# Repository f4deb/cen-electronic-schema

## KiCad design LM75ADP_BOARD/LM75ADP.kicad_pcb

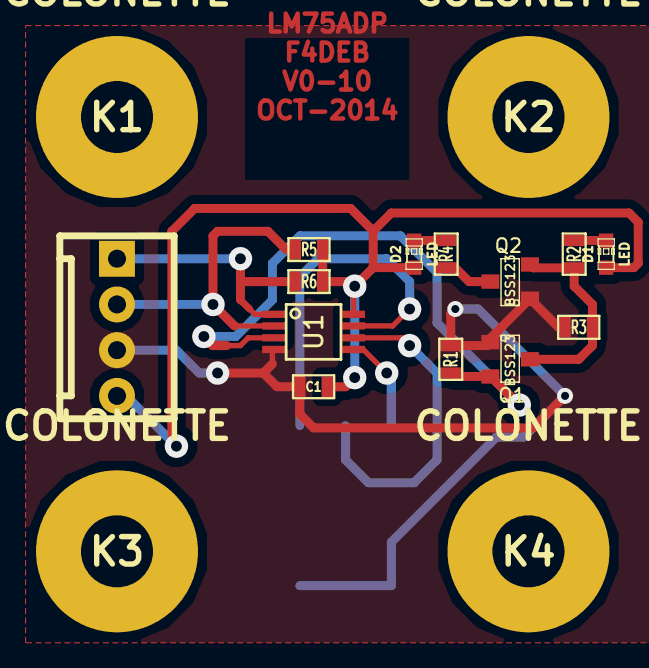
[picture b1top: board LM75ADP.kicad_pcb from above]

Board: 2 copper layers, 18 parts (1 on the bottom side), 12 nets.

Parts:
C1: 100n; SM0603_Capa
D1, D2: LED; LED-0603
K1, K2, K3, K4: COLONETTE
P1: CONN_4; KK-4
Q1, Q2: BSS123; SOT23
R1, R3: 470k; SM0603_Resistor
R2, R4: 3k3; SM0603_Resistor
R5, R6: 10k; SM0603_Resistor
SW1: SWITCH_X_4; SWCMS4
U1: LM75A; SSOP8

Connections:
/SCL: P1.2, R5.2, U1.2
/SDA: P1.1, R6.2, U1.1
GND: C1.2, P1.3, Q1.1, Q2.1, R1.2, R3.2, SW1.1, SW1.2, SW1.3, U1.4
unnamed: Q1.2, R1.1, U1.3
unnamed: Q1.3, Q2.2, R2.2, R3.1
unnamed: SW1.8, U1.5
unnamed: SW1.7, U1.6
unnamed: SW1.6, U1.7
unnamed: D2.2, R4.1
unnamed: Q2.3, R4.2
unnamed: D1.2, R2.1
VCC: C1.1, D1.1, D2.1, P1.4, R5.1, R6.1, U1.8

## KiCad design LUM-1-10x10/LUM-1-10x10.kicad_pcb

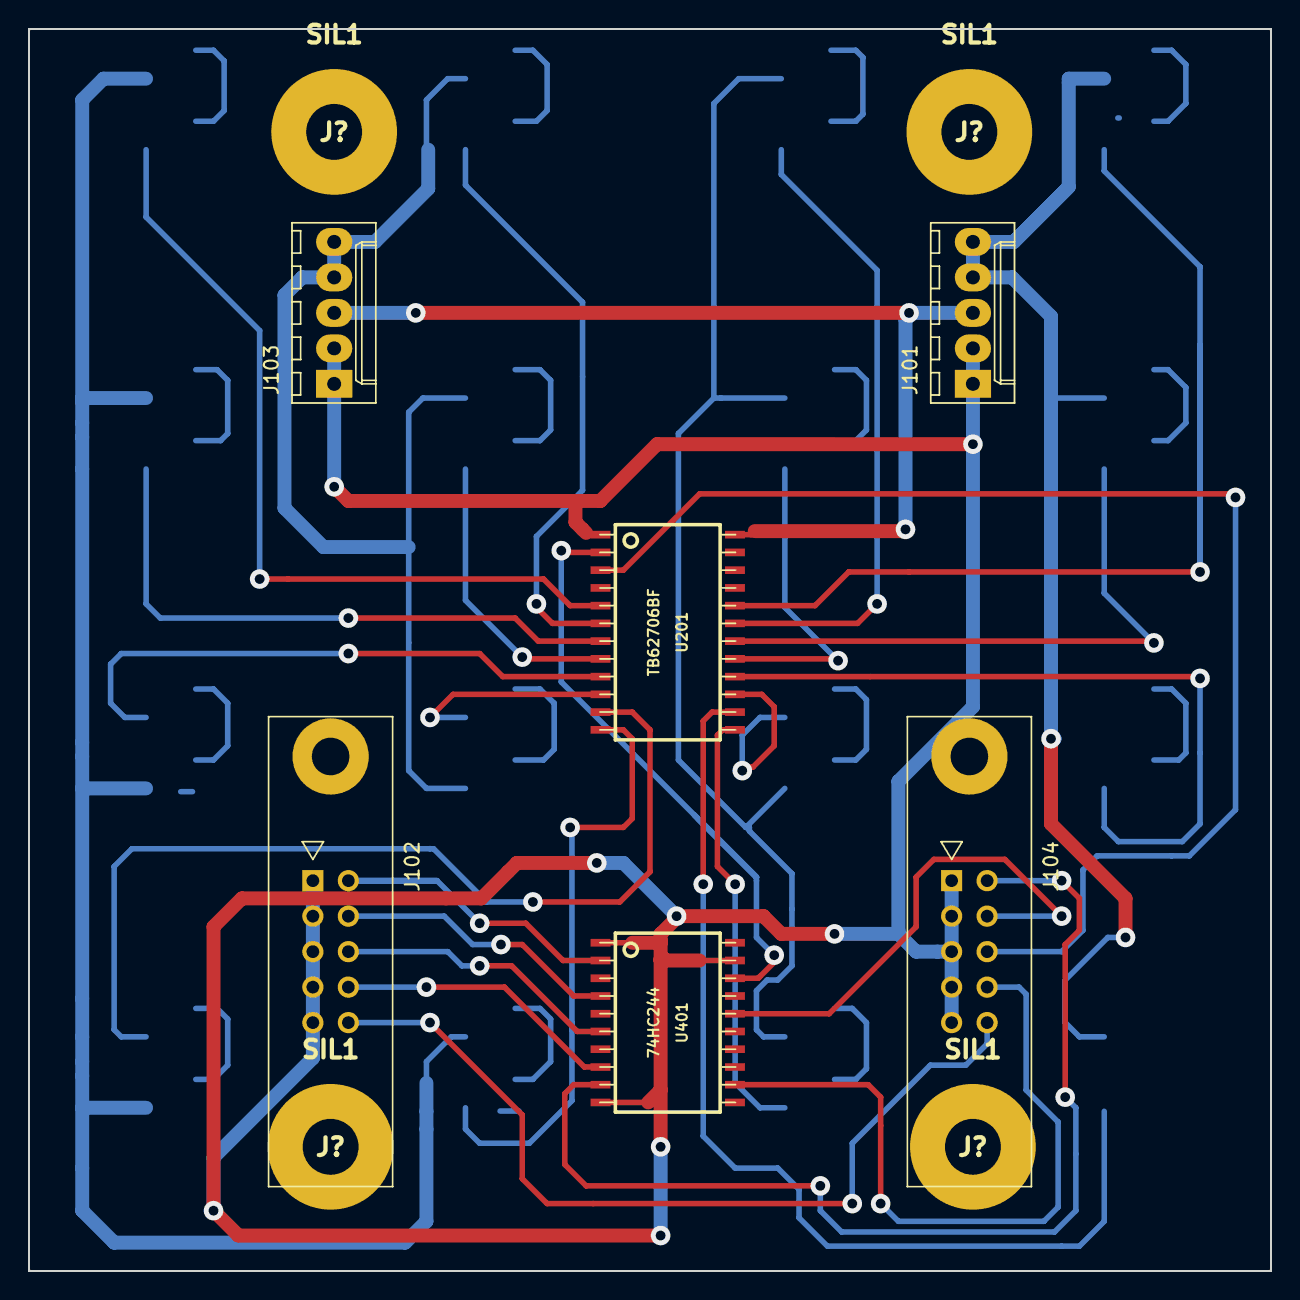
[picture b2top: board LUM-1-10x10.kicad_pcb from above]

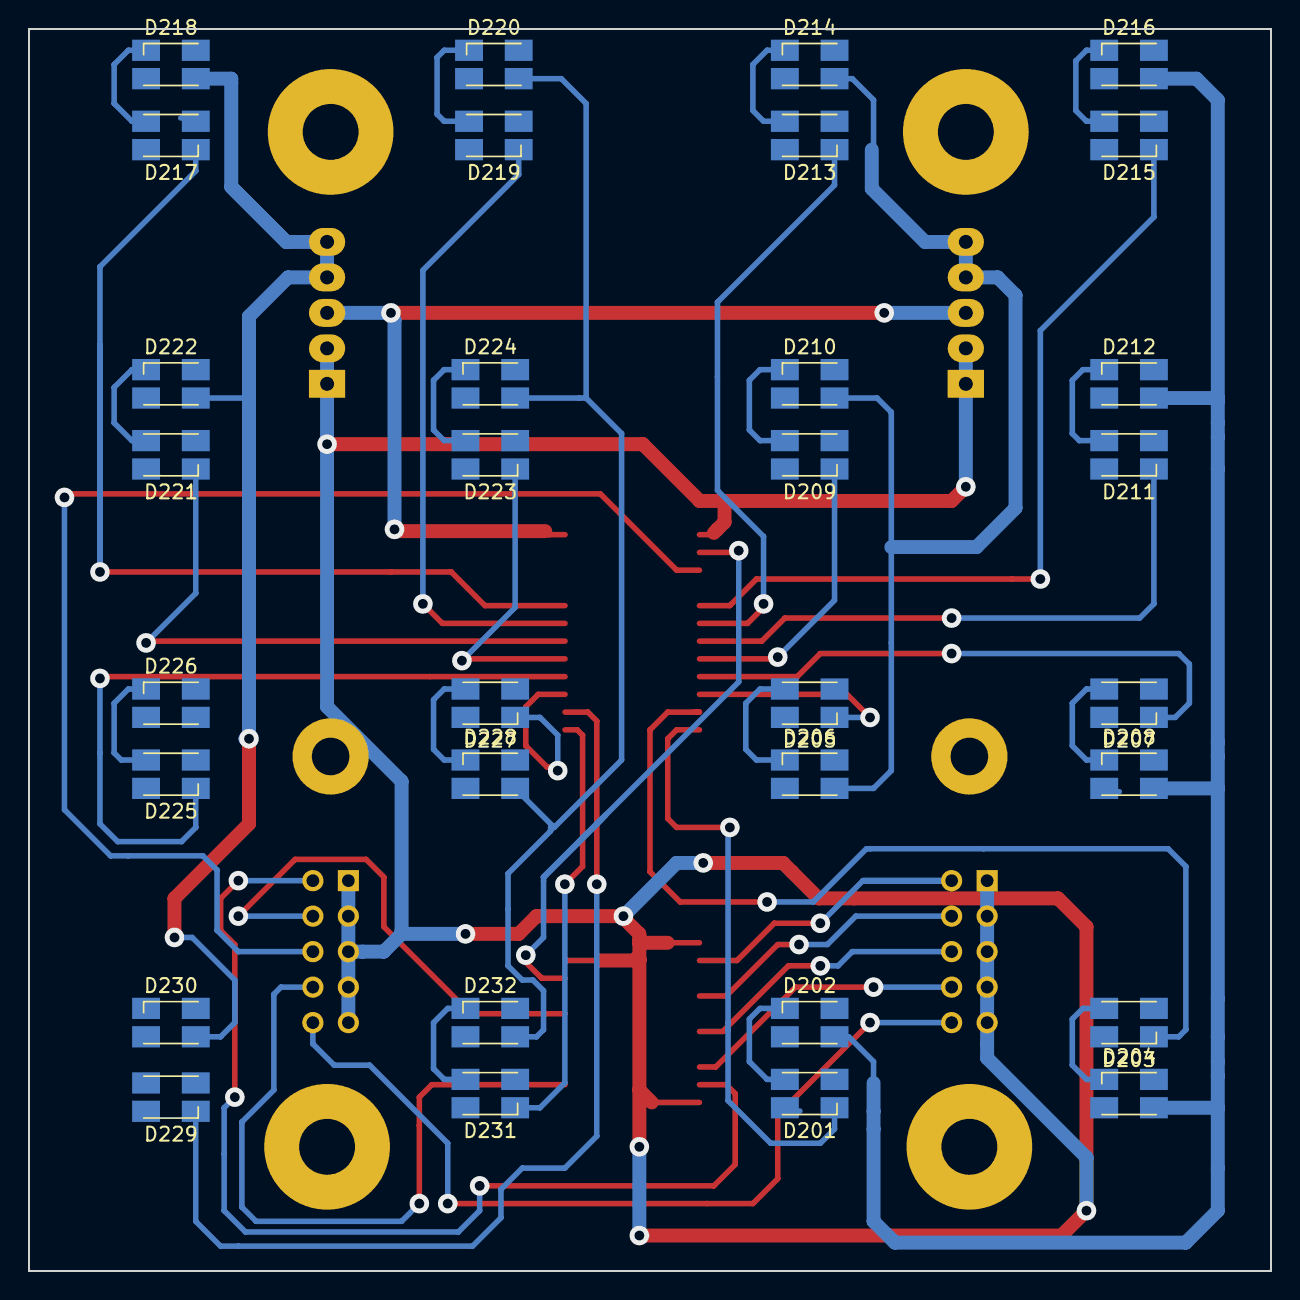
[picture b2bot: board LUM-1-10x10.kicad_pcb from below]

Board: 2 copper layers, 88.9 x 88.9 mm, 42 parts (32 on the bottom side), 45 nets.

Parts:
D201, D203, D205, D207, D209, D211, D213, D215, D217, D219, D221, D223, D225, D227, D229, D231: LED; LED_Cree-PLCC4_3.2x2.8mm_CCW
D202, D204, D206, D208, D210, D212, D214, D216, D218, D220, D222, D224, D226, D228, D230, D232: LED_PLCC_4; LED_Cree-PLCC4_3.2x2.8mm_CCW
J101, J103: CONN_01X05; Molex_KK-6410-05_05x2.54mm_Straight
J102, J104: CONN_02X05; he10-10d
J?: SIL1; COLONETTE
J?#2, J?#3, J?#4: SIL1; COLONETTE
U201: TB62706BF; soic-24
U401: 74HC244; soic-20

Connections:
+5V: D202.3, D204.3, D206.3, D208.3, D210.3, D212.3, D214.3, D216.3, D218.3, D220.3, D222.3, D224.3, D226.3, D228.3, D230.3, D232.3, J101.4, J101.5, J103.4, J103.5
+5VD: J101.3, J103.3, U201.24
/CLK: J104.6, U201.3, U401.14
/CLKA: J102.6, U401.6
/EN: J104.4, U401.16
/ENA: J102.4, U401.4
/LAT: J104.8, U401.12
/LATA: J102.8, U401.8
/RET: J102.10, J104.10
/S1: U201.2, U401.18
/S1A: J102.2, U401.2
/S5B: J104.2, U401.9
GND: J101.1, J101.2, J102.1, J102.3, J102.5, J102.7, J102.9, J103.1, J103.2, J104.1, J104.3, J104.5, J104.7, J104.9, U201.1, U401.1, U401.10, U401.19
unnamed: D201.1, U201.12
unnamed: D201.3, D202.1
unnamed: D203.1, U201.11
unnamed: D203.3, D204.1
unnamed: D205.1, U201.10
unnamed: D205.3, D206.1
unnamed: D207.1, U201.9
unnamed: D207.3, D208.1
unnamed: D209.1, U201.8
unnamed: D209.3, D210.1
unnamed: D211.1, U201.7
unnamed: D211.3, D212.1
unnamed: D213.1, U201.6
unnamed: D213.3, D214.1
unnamed: D215.1, U201.5
unnamed: D215.3, D216.1
unnamed: D217.1, U201.20
unnamed: D217.3, D218.1
unnamed: D219.1, U201.19
unnamed: D219.3, D220.1
unnamed: D221.1, U201.18
unnamed: D221.3, D222.1
unnamed: D223.1, U201.17
unnamed: D223.3, D224.1
unnamed: D225.1, U201.16
unnamed: D225.3, D226.1
unnamed: D227.1, U201.15
unnamed: D227.3, D228.1
unnamed: D229.1, U201.14
unnamed: D229.3, D230.1
unnamed: D231.1, U201.13
unnamed: D231.3, D232.1

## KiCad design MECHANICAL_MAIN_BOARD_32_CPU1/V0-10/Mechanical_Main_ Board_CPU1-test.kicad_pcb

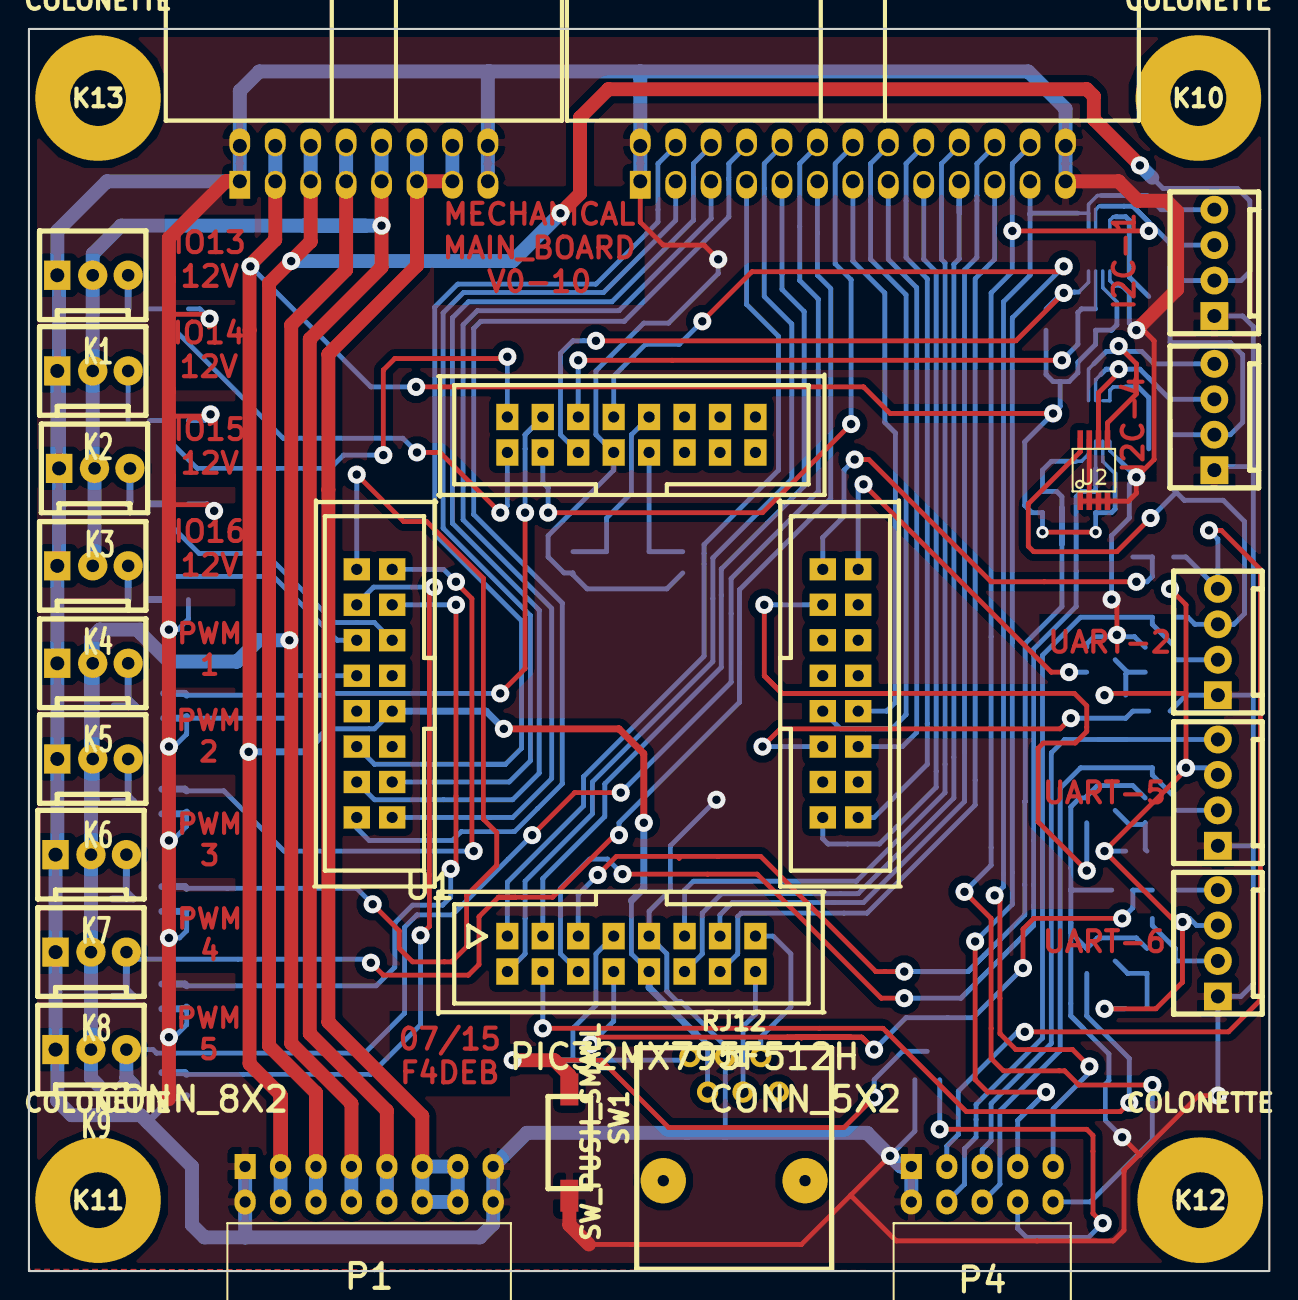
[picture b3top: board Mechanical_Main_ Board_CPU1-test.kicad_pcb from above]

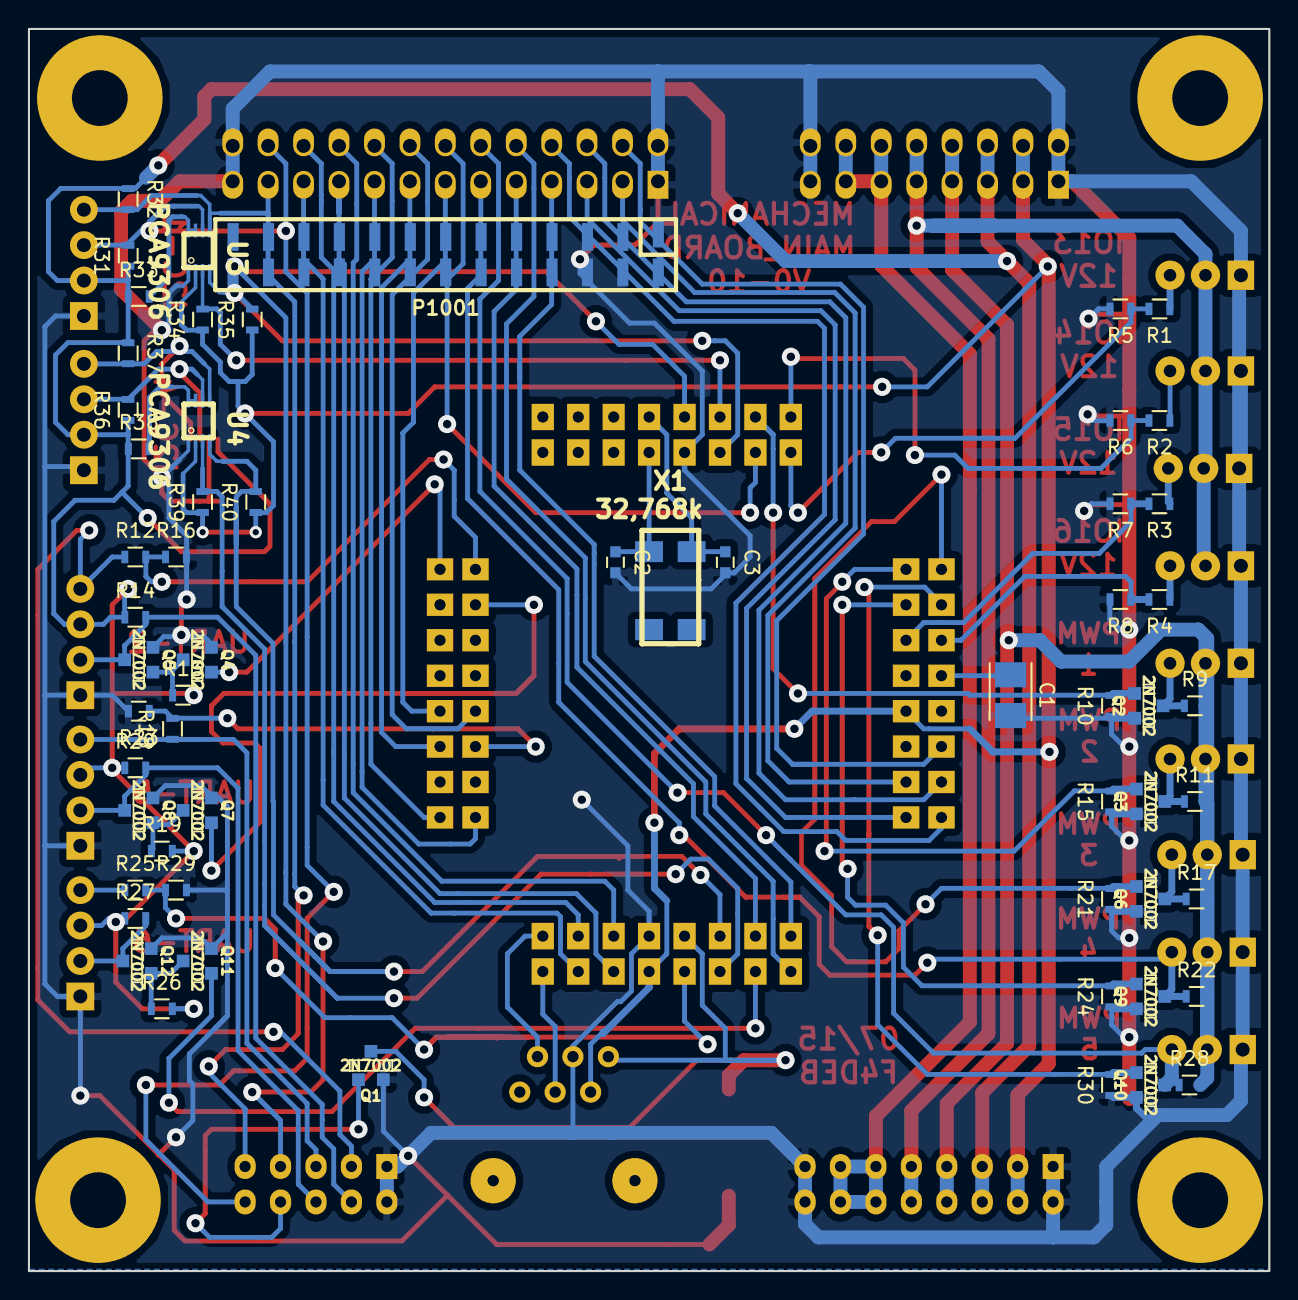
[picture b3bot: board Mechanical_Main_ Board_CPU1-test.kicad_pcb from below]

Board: 2 copper layers, 88.9 x 89.0 mm, 85 parts (59 on the bottom side), 68 nets.

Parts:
C1: 10u; TantalC_SizeB_EIA-3528_Reflow
C2, C3: 10p; C_0603
J1: RJ12
K1, K2, K3, K4, K5, K6, K7, K8, K9: CONN_3; KK-3
K10, K11, K12, K13: COLONETTE
P1: CONN_8X2; HE10-16-F-C
P2: CONN_8X2; vasch_strip_8x2_90
P3: CONN_13X2; vasch_strip_13x2_90
P4: CONN_5X2; HE10-10-F-C
P5, P6, P7, P8, P9: CONN_4; KK-4
P1001: CONN_13X2; pin_strip_13x2
Q1, Q2, Q3, Q4, Q5, Q6, Q7, Q8, Q9, Q10, Q11, Q12: 2N7002; SOT23GDS
R1, R3, R4: 47k; R_0603
R2: R47k; R_0603
R5, R6, R7, R8: 18k; R_0603
R9, R11, R13, R14, R17, R19, R20, R22, R26, R27, R28: 10k; R_0603
R10, R15, R21, R24, R30: 470k; R_0603
R12, R18, R25: 12k; R_0603
R16, R23, R29: 22k; R_0603
R31, R32, R34, R35, R36, R37, R39, R40: 2.1k; R_0603
R33, R38: 200k; R_0603
SW1: SW_PUSH_SMALL; SW2
U1: PIC32MX795F512H; PIC32_64
U2: 24C512; SSOP8
U3, U4: PCA9306; VSSOP-8
X1: 32,768k; LFXTAL003000

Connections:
+3V3: J1.2, P1.3, P1.4, P2.3, P2.4, R34.1, R35.1, R39.1, R40.1, U1.10, U1.57, U3.2, U4.2
+5V: K5.2, K6.2, K7.2, K8.2, K9.2, P1.7, P1.8, P2.7, P2.8, R9.2, R11.2, R17.2, R22.2, R28.2
+5VD: P1.5, P1.6, P2.5, P2.6, P5.3, P6.3, P7.3, P8.2, P9.2, R13.2, R14.1, R19.2, R20.1, R26.2, R27.1, R31.1, R32.1, R33.1, R36.1, R37.1, R38.1, U2.8
+12V: K1.2, K2.2, K3.2, K4.2, P1.9, P1.10, P2.9, P2.10
+15V: P1.11, P1.12, P1.13, P1.14, P2.11, P2.12, P2.13, P2.14
/INT1: P4.7, U1.42
/INT4: P3.14, P1001.14, U1.45
/IO1: P3.21, P1001.21, U1.14
/IO2: P3.22, P1001.22, U1.13
/IO3: P3.19, P1001.19, U1.12
/IO4: P3.20, P1001.20, U1.11
/IO5: P3.17, P1001.17, U1.17
/IO6: P3.18, P1001.18, U1.18
/IO7: P3.15, P1001.15, U1.22
/IO8: P3.16, P1001.16, U1.23
/IO9: P3.13, P1001.13, U1.24
/IO13: R1.2, R5.1, U1.47
/IO14: R2.2, R6.1, U1.48
/IO15: R3.2, R7.1, U1.53
/IO16: R4.2, R8.1, U1.54
/IO18: P3.4, P1001.4, U1.60
/IO19: P3.3, P1001.3, U1.61
/IO20: P3.6, P1001.6, U1.62
/IO21: P3.5, P1001.5, U1.63
/IO22: P3.8, P1001.8, U1.64
/IO23: P3.7, P1001.7, U1.1
/IO24: P3.10, P1001.10, U1.2
/IO25: P3.9, P1001.9, U1.3
/OC1: R10.2, U1.46
/OC1-5V: K5.3, R9.1
/OC2: R15.2, U1.49
/OC2-5V: K6.3, R11.1
/OC3: R21.2, U1.50
/OC4: R24.2, U1.51
/OC4-5V: K8.3, P3.11, P1001.11, R22.1
/OC5: R30.2, U1.52
/OC5-5V: K9.3, P3.12, P1001.12, R28.1
/PGEC1: J1.5, U1.15
/PGED1: J1.4, U1.16
/RSTA: J1.1, SW1.1, U1.7
/RX2: R12.2, R16.1, U1.31
/RX2-5V: P4.3, P5.4, R12.1
/RX5: R18.2, R23.1, U1.21
/RX5-5V: P4.5, P6.4, R18.1
/RX6: R25.2, R29.1, U1.8
/RX6-5V: P7.4, R25.1
/SCL1: R34.2, U1.44, U3.3
/SCL1-5V: P3.24, P4.10, P8.3, P1001.24, R31.2, U3.6
/SCL4: R39.2, U1.6, U4.3
/SCL4-5V: P9.3, R36.2, U2.6, U4.6
/SDA1: R35.2, U1.43, U3.4
/SDA1-5V: P3.23, P4.9, P8.4, P1001.23, R32.2, U3.5
/SDA4: R40.2, U1.5, U4.4
/SDA4-5V: P9.4, R37.2, U2.5, U4.5
/TX2-5V: P4.4, P5.2, R14.2
/TX5-5V: P4.6, P6.2, R20.2
/TX6-5V: P7.2, R27.2
GND: C1.2, C2.2, C3.2, J1.3, K1.1, K2.1, K3.1, K4.1, K5.1, K6.1, K7.1, K8.1, K9.1, P1.1, P1.2, P1.15, P1.16, P2.1, P2.2, P2.15, P2.16, P3.1, P3.2, P3.25, P3.26, P4.1, P4.2, P5.1, P6.1, P7.1, P8.1, P9.1, P1001.1, P1001.2, P1001.25, P1001.26, R5.2, R6.2, R7.2, R8.2, R10.1, R15.1, R16.2, R21.1, R23.2, R24.1, R29.2, R30.1, SW1.2, U1.9, U1.41, U2.1, U2.2, U2.3, U2.4, U2.7, U3.1, U4.1
unnamed: C1.1, U1.56
unnamed: C2.1, U1.39, X1.1
unnamed: C3.1, U1.40, X1.2
unnamed: K1.3, R1.1
unnamed: K2.3, R2.1
unnamed: K3.3, R3.1
unnamed: K4.3, R4.1
unnamed: K7.3, R17.1
unnamed: R33.2, U3.7, U3.8
unnamed: R38.2, U4.7, U4.8
